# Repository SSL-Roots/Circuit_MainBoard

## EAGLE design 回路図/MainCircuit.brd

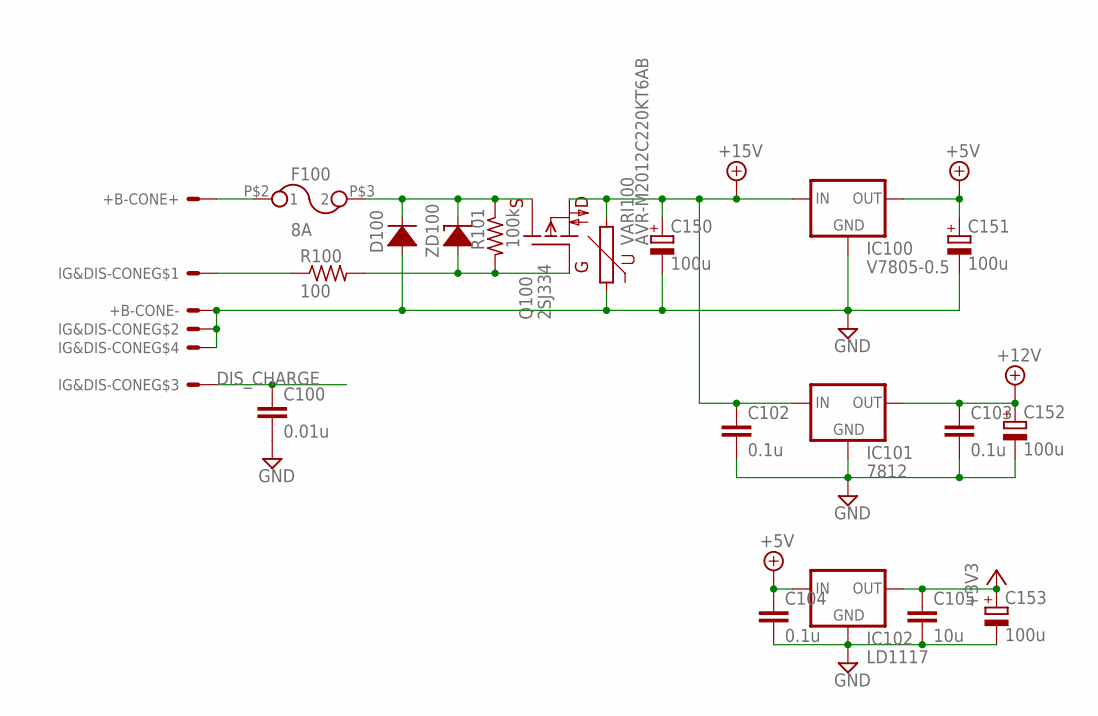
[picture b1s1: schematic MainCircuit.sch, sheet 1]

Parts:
+B-CONE: XT60
C100: 0.01u; C1608
C102, C103, C104: 0.1u; C1608
C105: 10u; C2012
C150, C151, C152, C153: 100u; E2,5-6
D100: DIODEDO214; DO214AC
FUSE: 8A; 3216
IC100: V7805-0.5
IC101: 7812; 78XXS
IC102: LD1117; SOT223
IG&DIS-CONE: 4B-XH-AB4B; B4B-XH-A
Q100: 2SJ334; TO220V
R100: 100; R1608
R101: 100k; R1608
VARI100: AVR-M2012C220KT6AB; 2012
ZD100: ZDIODEDO214AC; DO214AC

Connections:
+3V3: C105.1, C153.+, IC102.2 (OUT); also elsewhere on the board
+5V: C104.1, C151.+, IC100.+VOUT (OUT), IC102.3 (IN); also elsewhere on the board
+12V: C103.1, C152.+, IC101.OUT; also elsewhere on the board
+15V: C102.1, C150.+, IC100.+VIN (IN), IC101.IN, Q100.D, VARI100.2; also elsewhere on the board
DIS_CHARGE: C100.1, IG&DIS-CONE.3; also elsewhere on the board
GND: +B-CONE.-, C100.2, C102.2, C103.2, C104.2, C105.2, C150.-, C151.-, C152.-, C153.-, D100.A, IC100.GND, IC101.GND, IC102.1 (GND), IG&DIS-CONE.2, IG&DIS-CONE.4, VARI100.1; also elsewhere on the board
unnamed: IG&DIS-CONE.1, R100.1
unnamed: +B-CONE.+, FUSE.P$2 (1)
unnamed: D100.C, FUSE.P$3 (2), Q100.S, R101.1, ZD100.C (K)
unnamed: Q100.G, R100.2, R101.2, ZD100.A

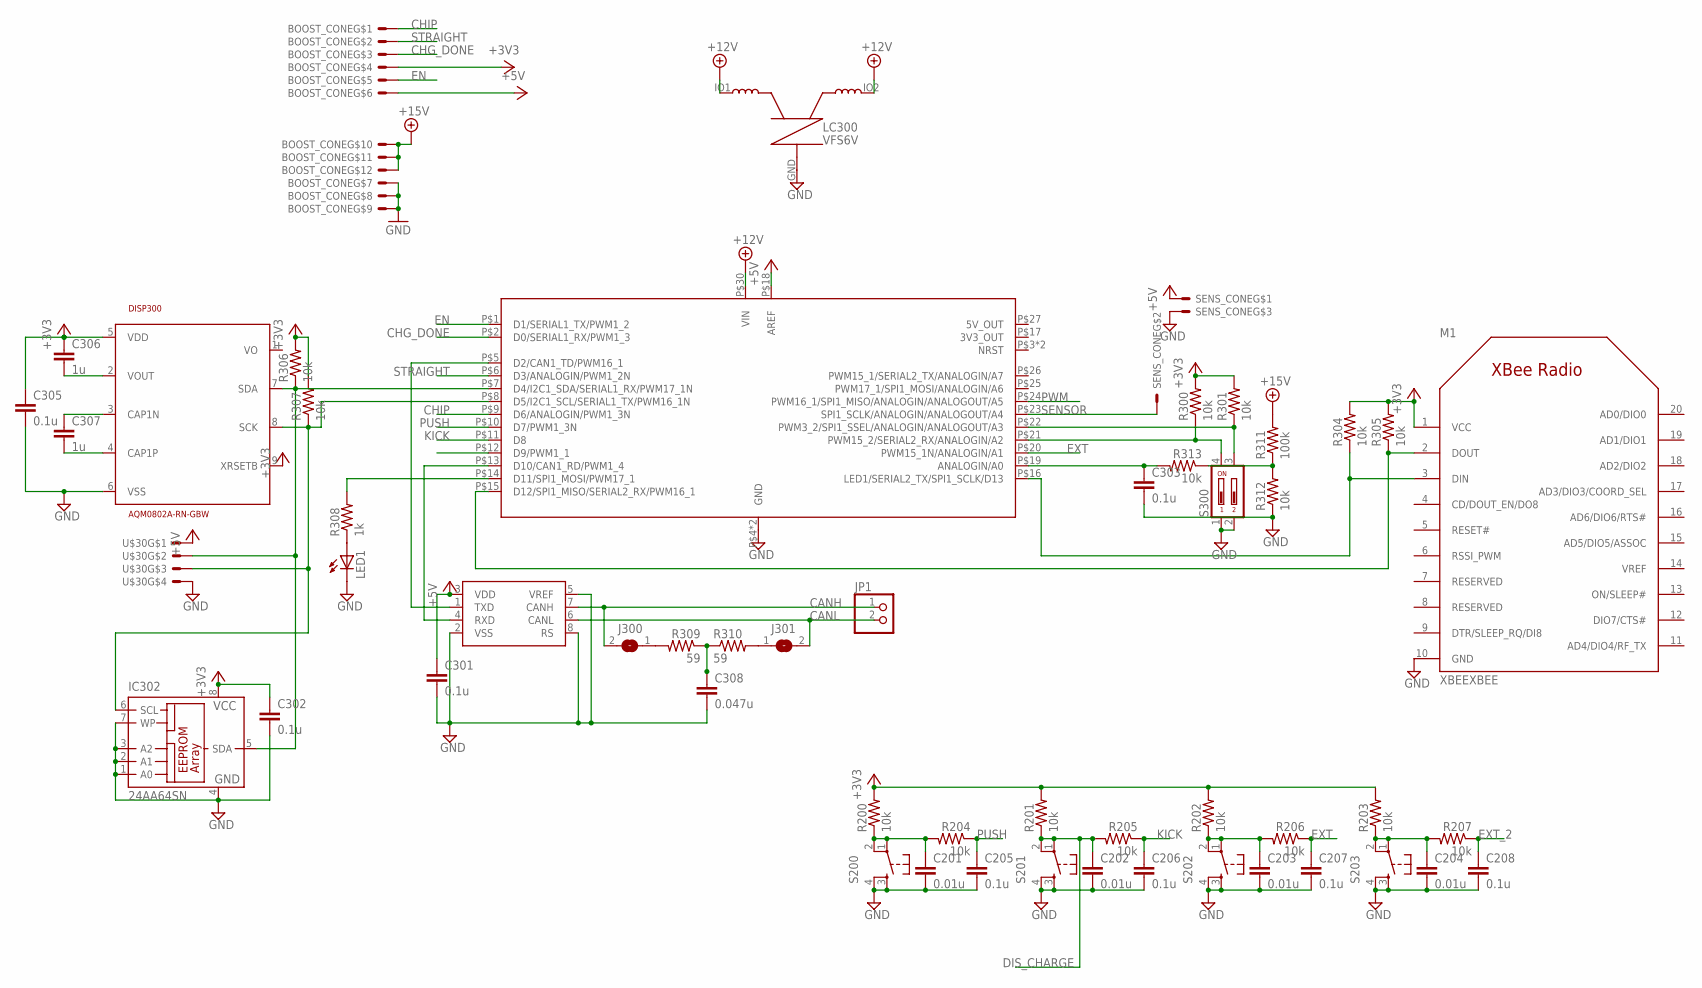
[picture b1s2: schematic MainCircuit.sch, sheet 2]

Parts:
BOOST_CONE: 12B-XH-AB12B; B12B-XH-A
C201, C202, C203, C204: 0.01u; C1608
C205, C206, C207, C208, C301, C302, C303, C305: 0.1u; C1608
C306, C307: 1u; C1608
C308: 0.047u; C1608
DISP300: AQM0802A-RN-GBW
IC300: NUCLEO-F303K8; NUCLEO-32
IC301: MCP2551; SOIC-8
IC302: 24AA64SN; SO-08
J300, J301: SJ
JP1: PINHD-1X2; 1X02
LC300: VFS6V
LED1: LED3MM
M1: XBEEXBEE; XBEE
R200, R201, R202, R203, R204, R205, R206, R207, R300, R301, R304, R305, R306, R307, R312, R313: 10k; R1608
R308: 1k; R1608
R309, R310: 59; R1608
R311: 100k; R1608
S200, S201, S202, S203: T-SWITCH; B3F-10XXS
S300: DIP02YL
SENS_CONE: 3B-XH-AB3B; B3B-XH-A
U$30: 4B-XH-AB4B; B4B-XH-A

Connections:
+3V3: BOOST_CONE.4, C302.1, C305.1, C306.1, DISP300.5 (VDD), DISP300.9 (XRSETB), IC302.8 (VCC), M1.1 (VCC), R200.2, R201.2, R202.2, R203.2, R300.2, R301.2, R304.2, R305.2, R306.2, R307.2; also elsewhere on the board
+5V: BOOST_CONE.6, C301.1, IC300.P$18 (AREF), IC301.3 (VDD), SENS_CONE.1, U$30.1; also elsewhere on the board
+12V: LC300.IO1; also elsewhere on the board
+12V": IC300.P$30 (VIN), LC300.IO2
+15V: BOOST_CONE.10, BOOST_CONE.11, BOOST_CONE.12, R311.2; also elsewhere on the board
CANH: IC301.7 (CANH), J300.2, JP1.1; also elsewhere on the board
CANL: IC301.6 (CANL), J301.2, JP1.2; also elsewhere on the board
CHG_DONE: BOOST_CONE.3, IC300.P$2 (D0/SERIAL1_RX/PWM1_3)
CHIP: BOOST_CONE.1, IC300.P$9 (D6/ANALOGIN/PWM1_3N)
DIS_CHARGE: C202.1, R201.1, R205.2, S201.1, S201.2 (P1); also elsewhere on the board
EN: BOOST_CONE.5, IC300.P$1 (D1/SERIAL1_TX/PWM1_2)
EXT: C207.1, IC300.P$20 (PWM15_1N/ANALOGIN/A1), R206.1
EXT_2: C208.1, IC300.P$12 (D9/PWM1_1), R207.1
GND: C201.2, C202.2, C203.2, C204.2, C205.2, C206.2, C207.2, C208.2, C301.2, C302.2, C303.2, C305.2, C308.2, DISP300.6 (VSS), IC300.P$4 (GND), IC300.P$29 (GND), IC301.2 (VSS), IC301.5 (VREF), IC301.8 (RS), IC302.1 (A0), IC302.2 (A1), IC302.3 (A2), IC302.4 (GND), IC302.7 (WP), LC300.GND, LED1.K (C), M1.10 (GND), R312.1, S200.3 (S), S200.4 (S1), S201.3 (S), S201.4 (S1), S202.3 (S), S202.4 (S1), S203.3 (S), S203.4 (S1), S300.1, S300.2, SENS_CONE.3, U$30.4; also elsewhere on the board
KICK: C206.1, IC300.P$11 (D8), R205.1
unnamed: C306.2, DISP300.2 (VOUT)
unnamed: C307.1, DISP300.3 (CAP1N)
unnamed: C307.2, DISP300.4 (CAP1P)
unnamed: C308.1, R309.1, R310.1
unnamed: J300.1, R309.2
unnamed: J301.1, R310.2
unnamed: R311.1, R312.2, R313.1
unnamed: IC300.P$22 (PWM3_2/SPI1_SSEL/ANALOGIN/ANALOGOUT/A3), R301.1, S300.3
unnamed: IC300.P$13 (D10/CAN1_RD/PWM1_4), IC301.4 (RXD)
unnamed: IC300.P$5 (D2/CAN1_TD/PWM16_1), IC301.1 (TXD)
unnamed: LED1.A, R308.1
unnamed: IC300.P$14 (D11/SPI1_MOSI/PWM17_1), R308.2
unnamed: IC300.P$15 (D12/SPI1_MISO/SERIAL2_RX/PWM16_1), M1.2 (DOUT), R305.1
unnamed: IC300.P$16 (LED1/SERIAL2_TX/SPI1_SCLK/D13), M1.3 (DIN), R304.1
unnamed: IC300.P$21 (PWM15_2/SERIAL2_RX/ANALOGIN/A2), R300.1, S300.4
unnamed: C303.1, IC300.P$19 (ANALOGIN/A0), R313.2
unnamed: C203.1, R202.1, R206.2, S202.1, S202.2 (P1)
unnamed: C204.1, R203.1, R207.2, S203.1, S203.2 (P1)
unnamed: C201.1, R200.1, R204.2, S200.1, S200.2 (P1)
PGND: BOOST_CONE.7, BOOST_CONE.8, BOOST_CONE.9; also elsewhere on the board
PUSH: C205.1, IC300.P$10 (D7/PWM1_3N), R204.1
PWM: IC300.P$24 (PWM16_1/SPI1_MISO/ANALOGIN/ANALOGOUT/A5); also elsewhere on the board
SCK: DISP300.8 (SCK), IC300.P$8 (D5/I2C1_SCL/SERIAL1_TX/PWM16_1N), IC302.6 (SCL), R307.1, U$30.3
SDA: DISP300.7 (SDA), IC300.P$7 (D4/I2C1_SDA/SERIAL1_RX/PWM17_1N), IC302.5 (SDA), R306.1, U$30.2
SENSOR: IC300.P$23 (SPI1_SCLK/ANALOGIN/ANALOGOUT/A4), SENS_CONE.2
STRAIGHT: BOOST_CONE.2, IC300.P$6 (D3/ANALOGIN/PWM1_2N)

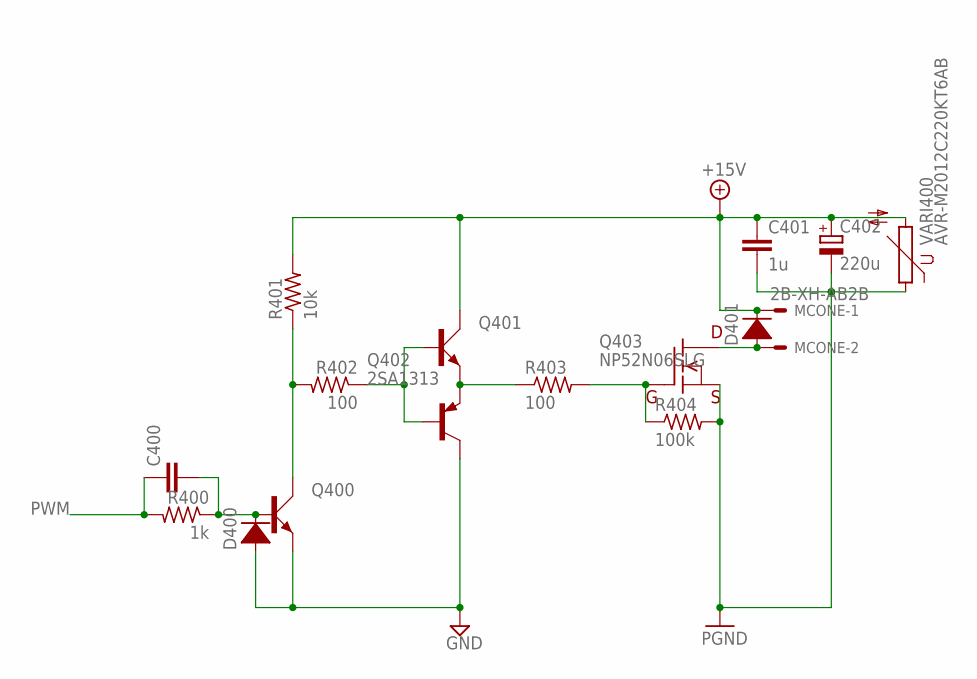
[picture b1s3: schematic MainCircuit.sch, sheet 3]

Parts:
C400: CC1608; C1608
C401: 1u; C1608
C402: 220u; E2,5-6
D400: DIODE1SS405; 1608
D401: DIODEDO214; DO214AC
MCONE: 2B-XH-AB2B; B2B-XH-A
Q400, Q401: 2SC3325; SOT23
Q402: 2SA1313; SOT23
Q403: NP52N06SLG; TO-252
R400: 1k; R1608
R401: 10k; R1608
R402, R403: 100; R1608
R404: 100k; R1608
VARI400: AVR-M2012C220KT6AB; 2012

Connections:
+15V: C401.1, C402.+, D401.C, MCONE.1, Q401.3 (C), R401.2, VARI400.2; also elsewhere on the board
GND: D400.A, Q400.2 (E), Q402.3 (C); also elsewhere on the board
unnamed: D401.A, MCONE.2, Q403.D
unnamed: Q401.2 (E), Q402.2 (E), R403.1
unnamed: Q403.G, R403.2, R404.1
unnamed: Q401.1 (B), Q402.1 (B), R402.1
unnamed: Q400.3 (C), R401.1, R402.2
unnamed: C400.2, D400.C, Q400.1 (B), R400.1
PGND: C401.2, C402.-, Q403.S, R404.2, VARI400.1; also elsewhere on the board
PWM: C400.1, R400.2; also elsewhere on the board

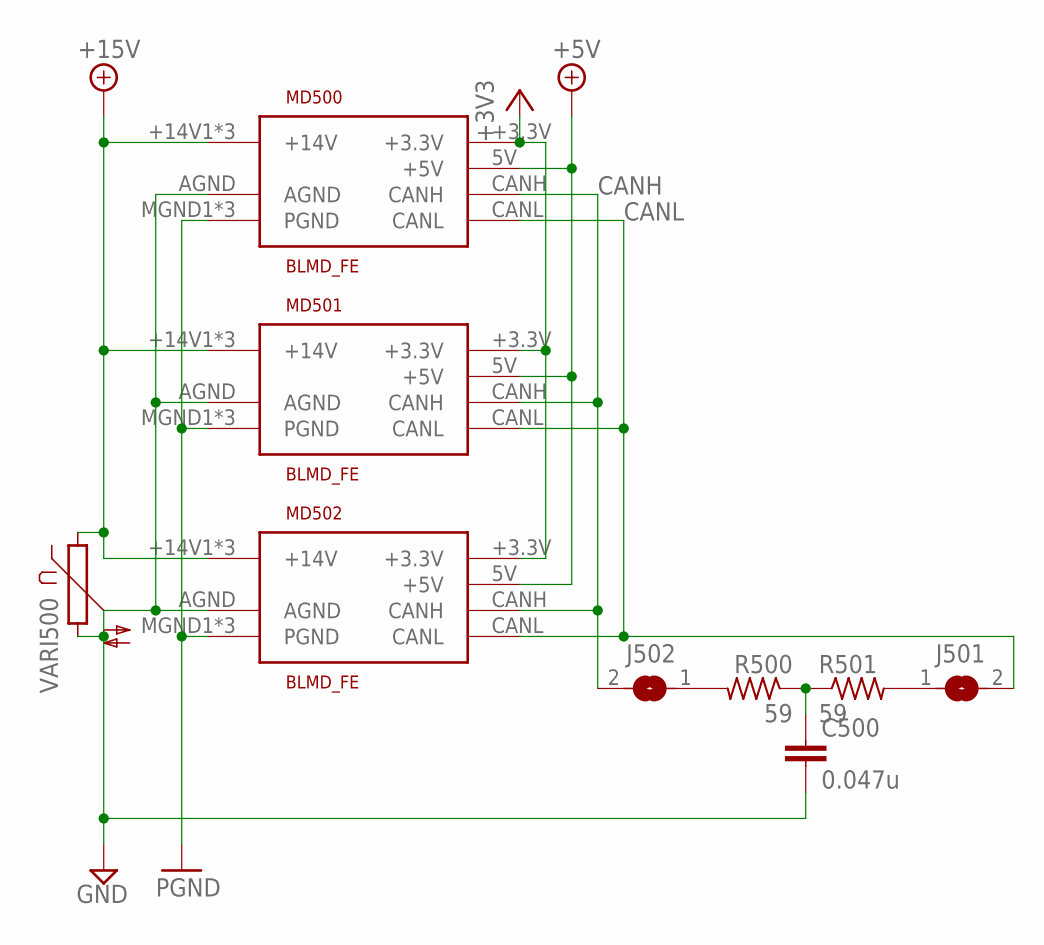
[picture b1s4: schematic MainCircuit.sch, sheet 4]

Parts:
C500: 0.047u; C1608
J501, J502: SJ
MD500, MD501, MD502: BLMD_FE; BLMD_TE
R500, R501: 59; R1608
VARI500: VARISTOR2012; 2012

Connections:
+3V3: MD500.+3.3V, MD501.+3.3V, MD502.+3.3V; also elsewhere on the board
+5V: MD500.5V (+5V), MD501.5V (+5V), MD502.5V (+5V); also elsewhere on the board
+15V: MD500.+14V1 (+14V), MD500.+14V2 (+14V), MD500.+14V3 (+14V), MD501.+14V1 (+14V), MD501.+14V2 (+14V), MD501.+14V3 (+14V), MD502.+14V1 (+14V), MD502.+14V2 (+14V), MD502.+14V3 (+14V), VARI500.1; also elsewhere on the board
CANH: J502.2, MD500.CANH, MD501.CANH, MD502.CANH; also elsewhere on the board
CANL: J501.2, MD500.CANL, MD501.CANL, MD502.CANL; also elsewhere on the board
GND: C500.2, MD500.AGND, MD501.AGND, MD502.AGND, VARI500.2; also elsewhere on the board
unnamed: C500.1, R500.1, R501.1
unnamed: J502.1, R500.2
unnamed: J501.1, R501.2
PGND: MD500.MGND1 (PGND), MD500.MGND2 (PGND), MD500.MGND3 (PGND), MD501.MGND1 (PGND), MD501.MGND2 (PGND), MD501.MGND3 (PGND), MD502.MGND1 (PGND), MD502.MGND2 (PGND), MD502.MGND3 (PGND); also elsewhere on the board

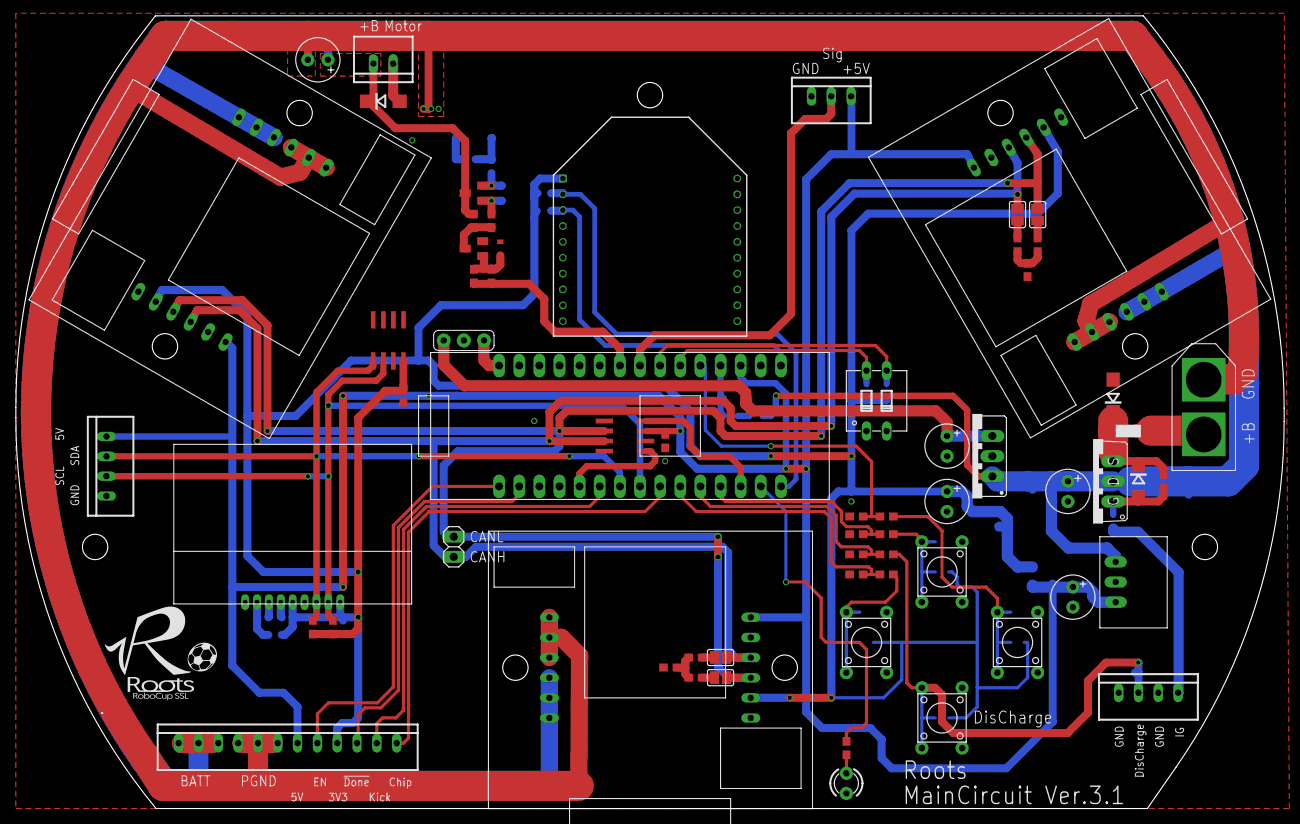
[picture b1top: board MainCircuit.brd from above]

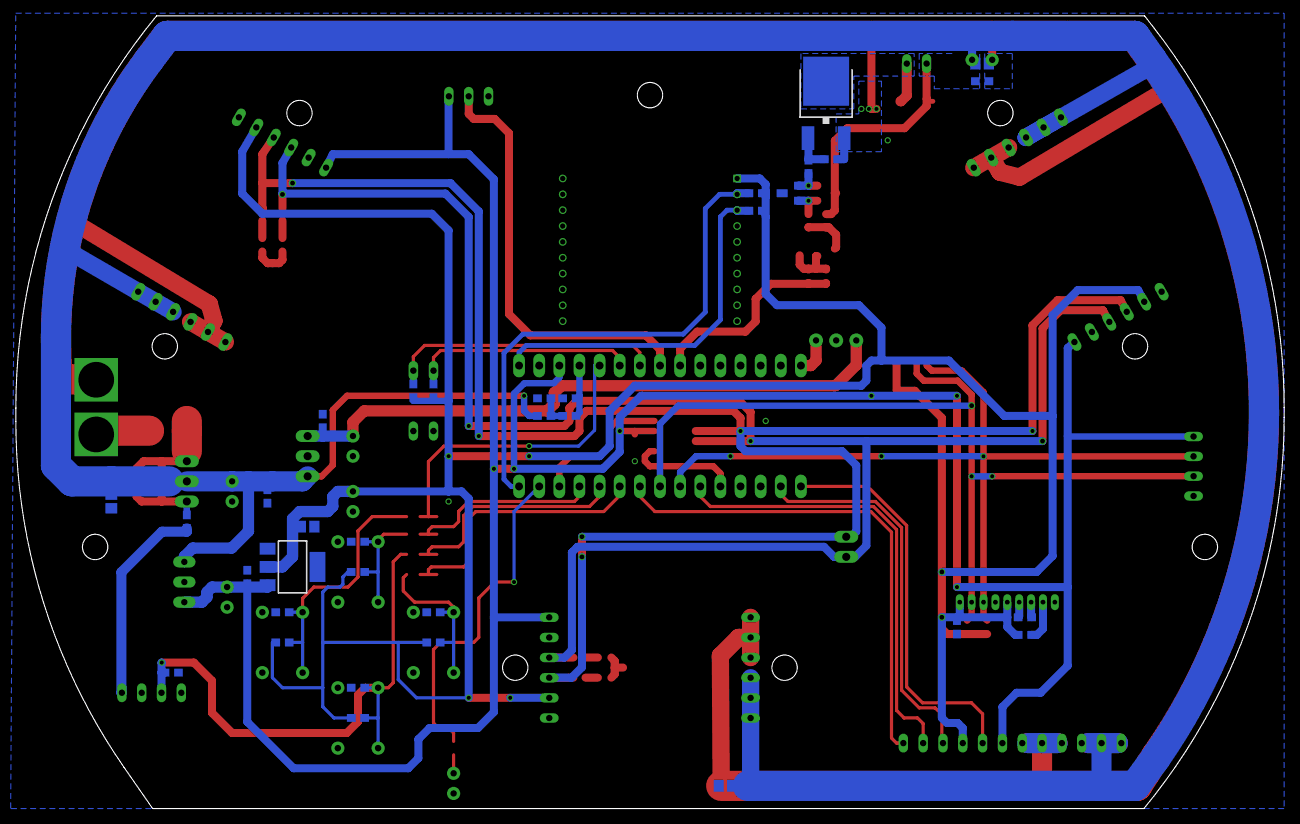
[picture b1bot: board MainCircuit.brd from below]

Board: 2 copper layers, 160.0 x 100.0 mm, 100 parts (34 on the bottom side), 54 nets.

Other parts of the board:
U$106: ROOTS

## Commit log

2017-08-02 メイン基板の回路図・運用・作成マニュアル
